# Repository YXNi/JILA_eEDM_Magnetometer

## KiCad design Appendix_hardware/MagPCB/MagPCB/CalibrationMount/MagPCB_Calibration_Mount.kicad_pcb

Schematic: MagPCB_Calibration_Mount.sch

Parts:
HCONN1: HOST_CONN
P1: BOLT_CONN_SINGLE_SUPP
R1: Thermistor
R2: 30k

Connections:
AIN: HCONN1.5 (AIN), R1.2, R2.1
GND: HCONN1.2 (GND), P1.2, R2.2
SCL: HCONN1.3 (SCL), P1.3
SDA: HCONN1.4 (SDA), P1.4
VDD: HCONN1.1 (VDD), P1.1, R1.1

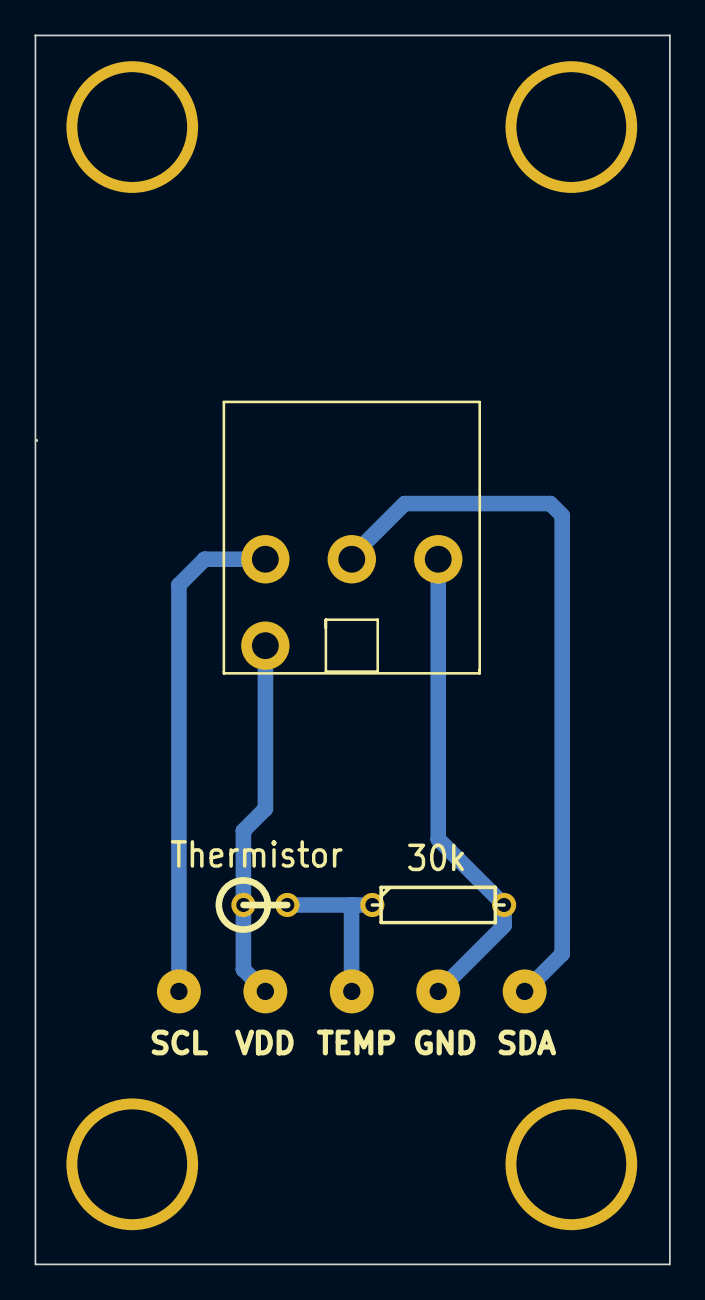
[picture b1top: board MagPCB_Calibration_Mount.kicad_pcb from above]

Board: 2 copper layers, 36.7 x 71.1 mm, 6 parts (0 on the bottom side), 5 nets.

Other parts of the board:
CALIB_MOUNT_HOLES: VAL**; CALIB_MOUNT_HOLES
CALIB_MOUNT_HOLES#2: VAL**; CALIB_MOUNT_HOLES

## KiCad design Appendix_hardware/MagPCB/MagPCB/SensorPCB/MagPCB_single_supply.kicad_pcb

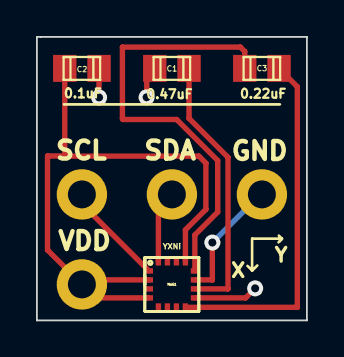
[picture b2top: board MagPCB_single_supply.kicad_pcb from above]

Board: 2 copper layers, 15.0 x 15.8 mm, 4 parts (0 on the bottom side), 5 nets.

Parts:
C1, C2, C3: c_0805
MAG1: HMC5883

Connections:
GND: C1.2, C2.2, MAG1.9, MAG1.11
unnamed: C1.1, MAG1.10
unnamed: C3.2, MAG1.12
unnamed: C3.1, MAG1.8
VDD: C2.1, MAG1.2, MAG1.4, MAG1.13

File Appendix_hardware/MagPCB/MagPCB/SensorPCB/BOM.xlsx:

Best Practice Bill of Materials (BOM) Template
1. Reference Designators - Place all designators with the same part number in o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
2. Description Value Package - Advanced Assembly's system perfers this to be co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
3. Alternate Part Numbers - Place in additional columns to the right on the sam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
4. Do Not Install (DNI) Parts - Indicate quantity zero and/or add DNI column
5. Notes - Place in additional column on the same line
6. Refrain from using merged cells
*Please contact your account executive with any questions.*
 |  |  |  | êAuto-populates as you fill in the previous cellsê
Mfg Part # | Description | Value | Pkg | Description Value Pkg *AAPCB Format* | Ref. Des. | Qty | DNI | Notes | Mfg (Optional) | Vendor (Optional) | Vendor Part # (Optional) | Alternate Mfg Part # (Optional) | Type (Optional)
VJ0805Y224KNXAT | CAP | .22uF@25V | 805 | CAP .22uF@25V 805 | C3 | 1 |  |  | Vishay
VJ0805Y104KNAAT | CAP | 0.1UF 25V 10% | 805 | CAP 0.1UF 25V 10% 805 | C2 | 1 |  |  | Vishay
HMC5883L-TR | Magnetic censor |  | 16LCC SMD | Magnetic censor 16LCC SMD | MAG1 | 1 |  |  | Honeywell | Digi-Key | 342-1082-1-ND
UMK325F475ZH-T | CAP | 4.7uF@50V 10% | 1210 | CAP 4.7uF@50V 10% 1210 | C1 | 1 |  |  | Taiyo-yuden | Digi-Key | 587-1389-1-ND

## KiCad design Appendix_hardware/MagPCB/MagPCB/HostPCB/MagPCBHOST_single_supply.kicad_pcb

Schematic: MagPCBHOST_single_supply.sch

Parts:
C1: 10nF
MUX1: MAX4617
P1, P2, P3, P4, P5, P6, P7, P8: BOLT_CONN_SINGLE_SUPP
P9: HOST_CONNECTOR_SINGLE_SUPP
R1, R2, R3, R4: 1k
R5: 30k
TEMP1: TEMP

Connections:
A: MUX1.11 (A), P9.5 (A), R4.1
B: MUX1.10 (B), P9.6 (B), R3.1
C: MUX1.9 (C), P9.7 (C), R2.1
EN: MUX1.6 (EN), P9.8 (EN), R1.1
GND: C1.1, MUX1.8 (GND), P1.2, P2.2, P3.2, P4.2, P5.2, P6.2, P7.2, P8.2, P9.4 (GND), R1.2, R2.2, R3.2, R4.2, R5.2
SCL: P1.3, P2.3, P3.3, P4.3, P5.3, P6.3, P7.3, P8.3, P9.1 (SCL)
SDA: MUX1.3 (X), P9.2 (SCA)
SDA1: MUX1.15 (X2), P1.4
SDA2: MUX1.14 (X1), P2.4
SDA3: MUX1.13 (X0), P3.4
SDA4: MUX1.12 (X3), P4.4
SDA5: MUX1.2 (X6), P5.4
SDA6: MUX1.4 (X7), P6.4
SDA7: MUX1.1 (X4), P7.4
SDA8: MUX1.5 (X5), P8.4
TEMP: P9.9 (TEMP), R5.1, TEMP1.2
VDD: C1.2, MUX1.16 (VCC), P1.1, P2.1, P3.1, P4.1, P5.1, P6.1, P7.1, P8.1, P9.3 (VCC), TEMP1.1

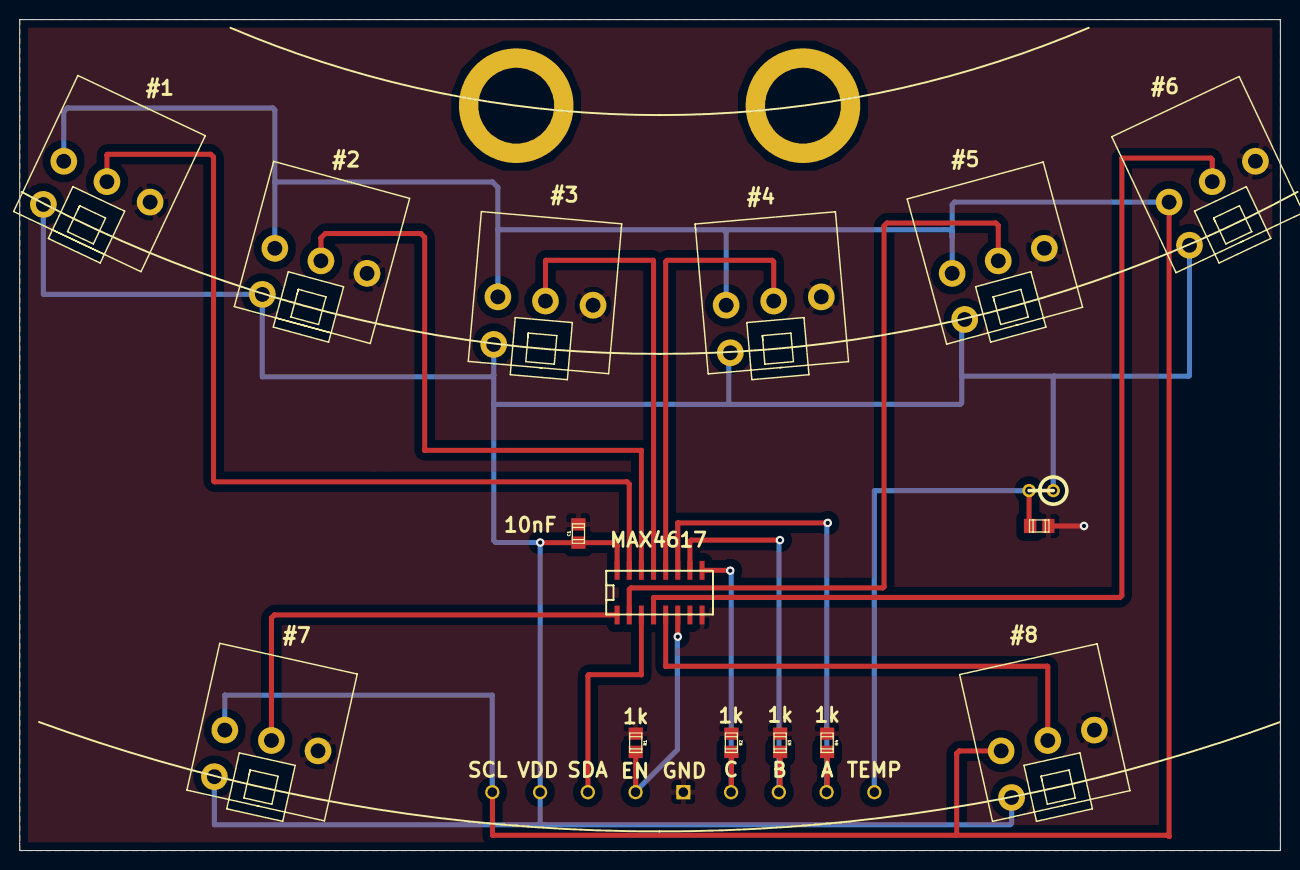
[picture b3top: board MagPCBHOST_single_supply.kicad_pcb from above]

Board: 2 copper layers, 132.0 x 87.0 mm, 17 parts (0 on the bottom side), 17 nets.

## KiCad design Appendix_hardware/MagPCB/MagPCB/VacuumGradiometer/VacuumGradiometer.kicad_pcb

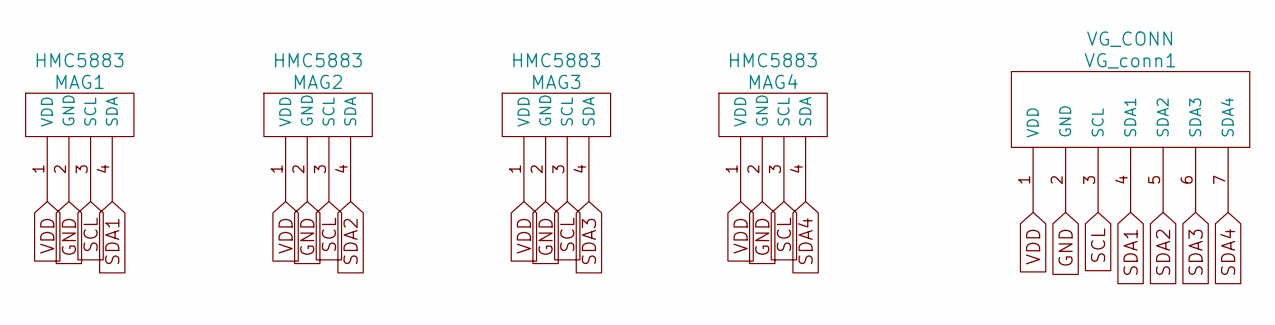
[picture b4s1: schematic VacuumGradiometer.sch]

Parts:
MAG1, MAG2, MAG3, MAG4: HMC5883
VG_conn1: VG_CONN

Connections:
GND: MAG1.2 (GND), MAG2.2 (GND), MAG3.2 (GND), MAG4.2 (GND), VG_conn1.2 (GND)
SCL: MAG1.3 (SCL), MAG2.3 (SCL), MAG3.3 (SCL), MAG4.3 (SCL), VG_conn1.3 (SCL)
SDA1: MAG1.4 (SDA), VG_conn1.4 (SDA1)
SDA2: MAG2.4 (SDA), VG_conn1.5 (SDA2)
SDA3: MAG3.4 (SDA), VG_conn1.6 (SDA3)
SDA4: MAG4.4 (SDA), VG_conn1.7 (SDA4)
VDD: MAG1.1 (VDD), MAG2.1 (VDD), MAG3.1 (VDD), MAG4.1 (VDD), VG_conn1.1 (VDD)

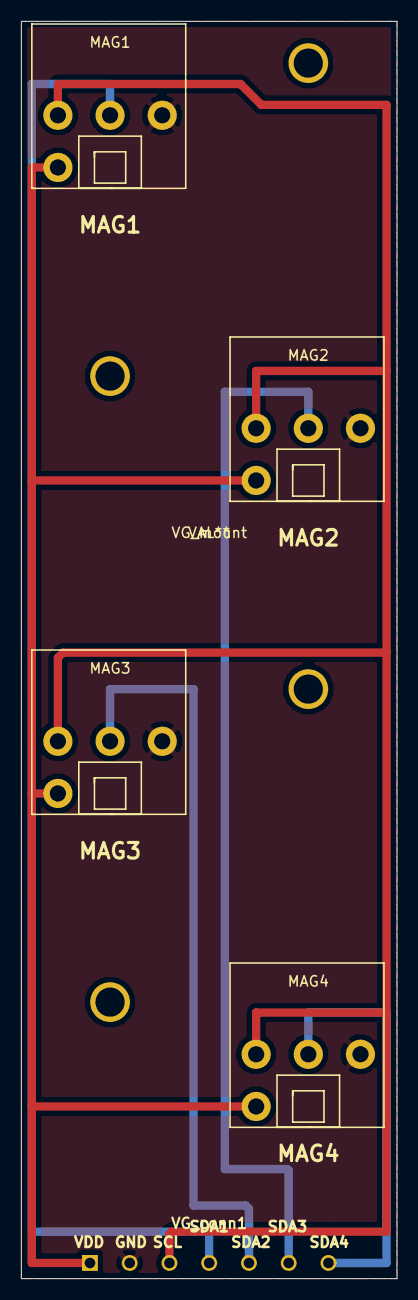
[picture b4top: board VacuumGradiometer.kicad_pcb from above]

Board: 2 copper layers, 36.0 x 120.5 mm, 6 parts (0 on the bottom side), 7 nets.

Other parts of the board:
VG_mount: VAL**; VG_mount

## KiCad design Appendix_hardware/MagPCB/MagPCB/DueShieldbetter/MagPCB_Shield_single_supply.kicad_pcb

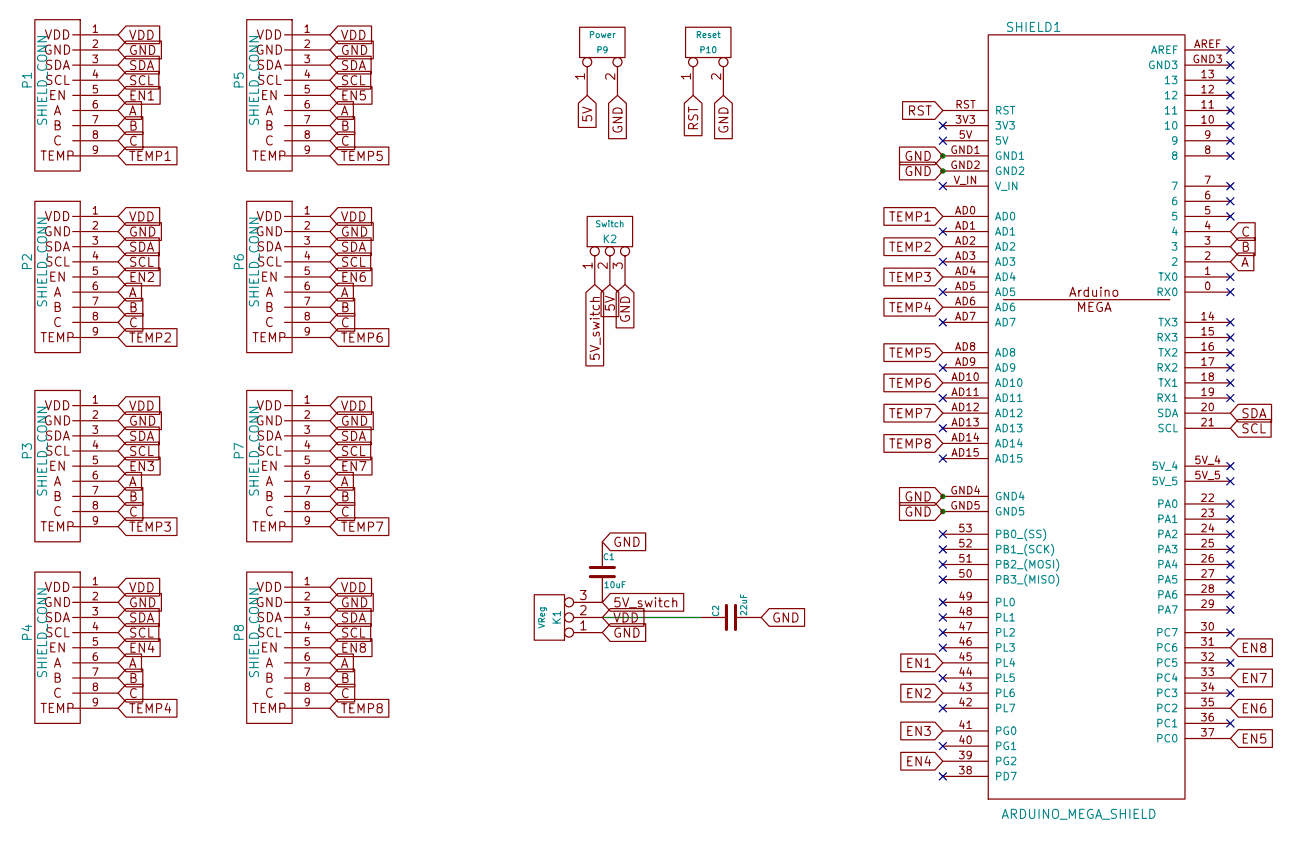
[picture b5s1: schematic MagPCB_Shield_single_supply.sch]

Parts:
C1: 10uF
C2: 22uF
K1: VReg
K2: Switch
P1, P2, P3, P4, P5, P6, P7, P8: SHIELD_CONN
P9: Power
P10: Reset
SHIELD1: ARDUINO_MEGA_SHIELD

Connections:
5V: K2.2 (PM), P9.1
5V_switch: C1.2, K1.3, K2.1
A: P1.6 (A), P2.6 (A), P3.6 (A), P4.6 (A), P5.6 (A), P6.6 (A), P7.6 (A), P8.6 (A), SHIELD1.2
B: P1.7 (B), P2.7 (B), P3.7 (B), P4.7 (B), P5.7 (B), P6.7 (B), P7.7 (B), P8.7 (B), SHIELD1.3
C: P1.8 (C), P2.8 (C), P3.8 (C), P4.8 (C), P5.8 (C), P6.8 (C), P7.8 (C), P8.8 (C), SHIELD1.4
EN1: P1.5 (EN), SHIELD1.45 (PL4)
EN2: P2.5 (EN), SHIELD1.43 (PL6)
EN3: P3.5 (EN), SHIELD1.41 (PG0)
EN4: P4.5 (EN), SHIELD1.39 (PG2)
EN5: P5.5 (EN), SHIELD1.37 (PC0)
EN6: P6.5 (EN), SHIELD1.35 (PC2)
EN7: P7.5 (EN), SHIELD1.33 (PC4)
EN8: P8.5 (EN), SHIELD1.31 (PC6)
GND: C1.1, C2.2, K1.1, K2.3, P1.2 (GND), P2.2 (GND), P3.2 (GND), P4.2 (GND), P5.2 (GND), P6.2 (GND), P7.2 (GND), P8.2 (GND), P9.2 (PM), P10.2 (PM), SHIELD1.GND1, SHIELD1.GND2, SHIELD1.GND4, SHIELD1.GND5
RST: P10.1, SHIELD1.RST
SCL: P1.4 (SCL), P2.4 (SCL), P3.4 (SCL), P4.4 (SCL), P5.4 (SCL), P6.4 (SCL), P7.4 (SCL), P8.4 (SCL), SHIELD1.21 (SCL)
SDA: P1.3 (SDA), P2.3 (SDA), P3.3 (SDA), P4.3 (SDA), P5.3 (SDA), P6.3 (SDA), P7.3 (SDA), P8.3 (SDA), SHIELD1.20 (SDA)
TEMP1: P1.9 (TEMP), SHIELD1.AD0
TEMP2: P2.9 (TEMP), SHIELD1.AD2
TEMP3: P3.9 (TEMP), SHIELD1.AD4
TEMP4: P4.9 (TEMP), SHIELD1.AD6
TEMP5: P5.9 (TEMP), SHIELD1.AD8
TEMP6: P6.9 (TEMP), SHIELD1.AD10
TEMP7: P7.9 (TEMP), SHIELD1.AD12
TEMP8: P8.9 (TEMP), SHIELD1.AD14
VDD: C2.1, K1.2 (PM), P1.1 (VDD), P2.1 (VDD), P3.1 (VDD), P4.1 (VDD), P5.1 (VDD), P6.1 (VDD), P7.1 (VDD), P8.1 (VDD)

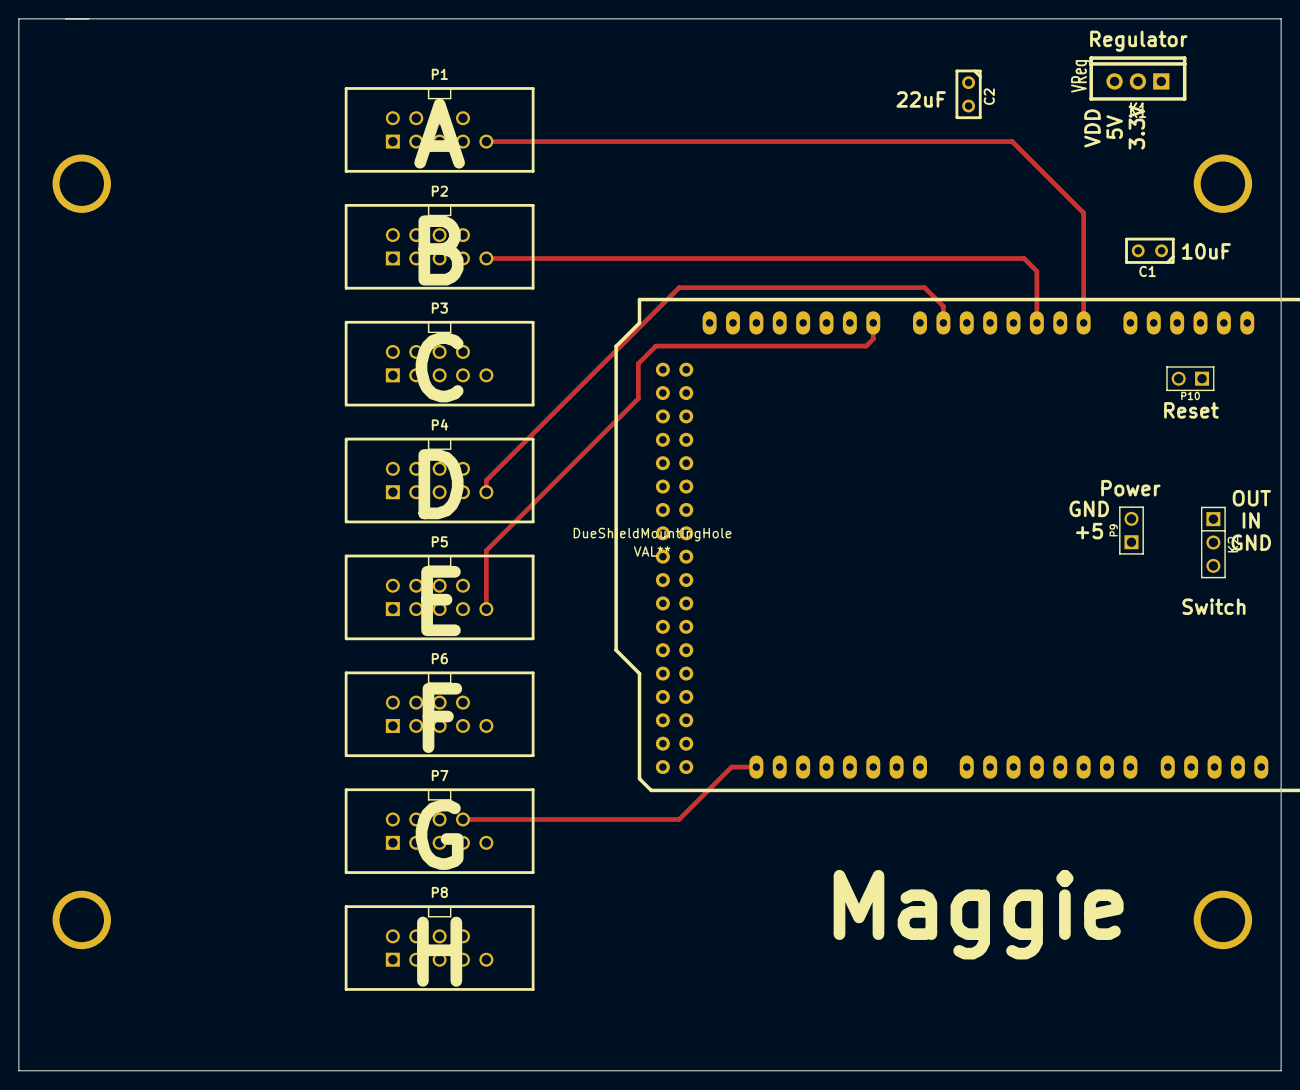
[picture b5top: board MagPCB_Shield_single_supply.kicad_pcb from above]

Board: 2 copper layers, 137.2 x 114.3 mm, 16 parts (0 on the bottom side), 26 nets.

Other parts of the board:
DueShieldMountingHole: VAL**; DueShieldMountingHole

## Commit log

2017-04-03 Hub1
